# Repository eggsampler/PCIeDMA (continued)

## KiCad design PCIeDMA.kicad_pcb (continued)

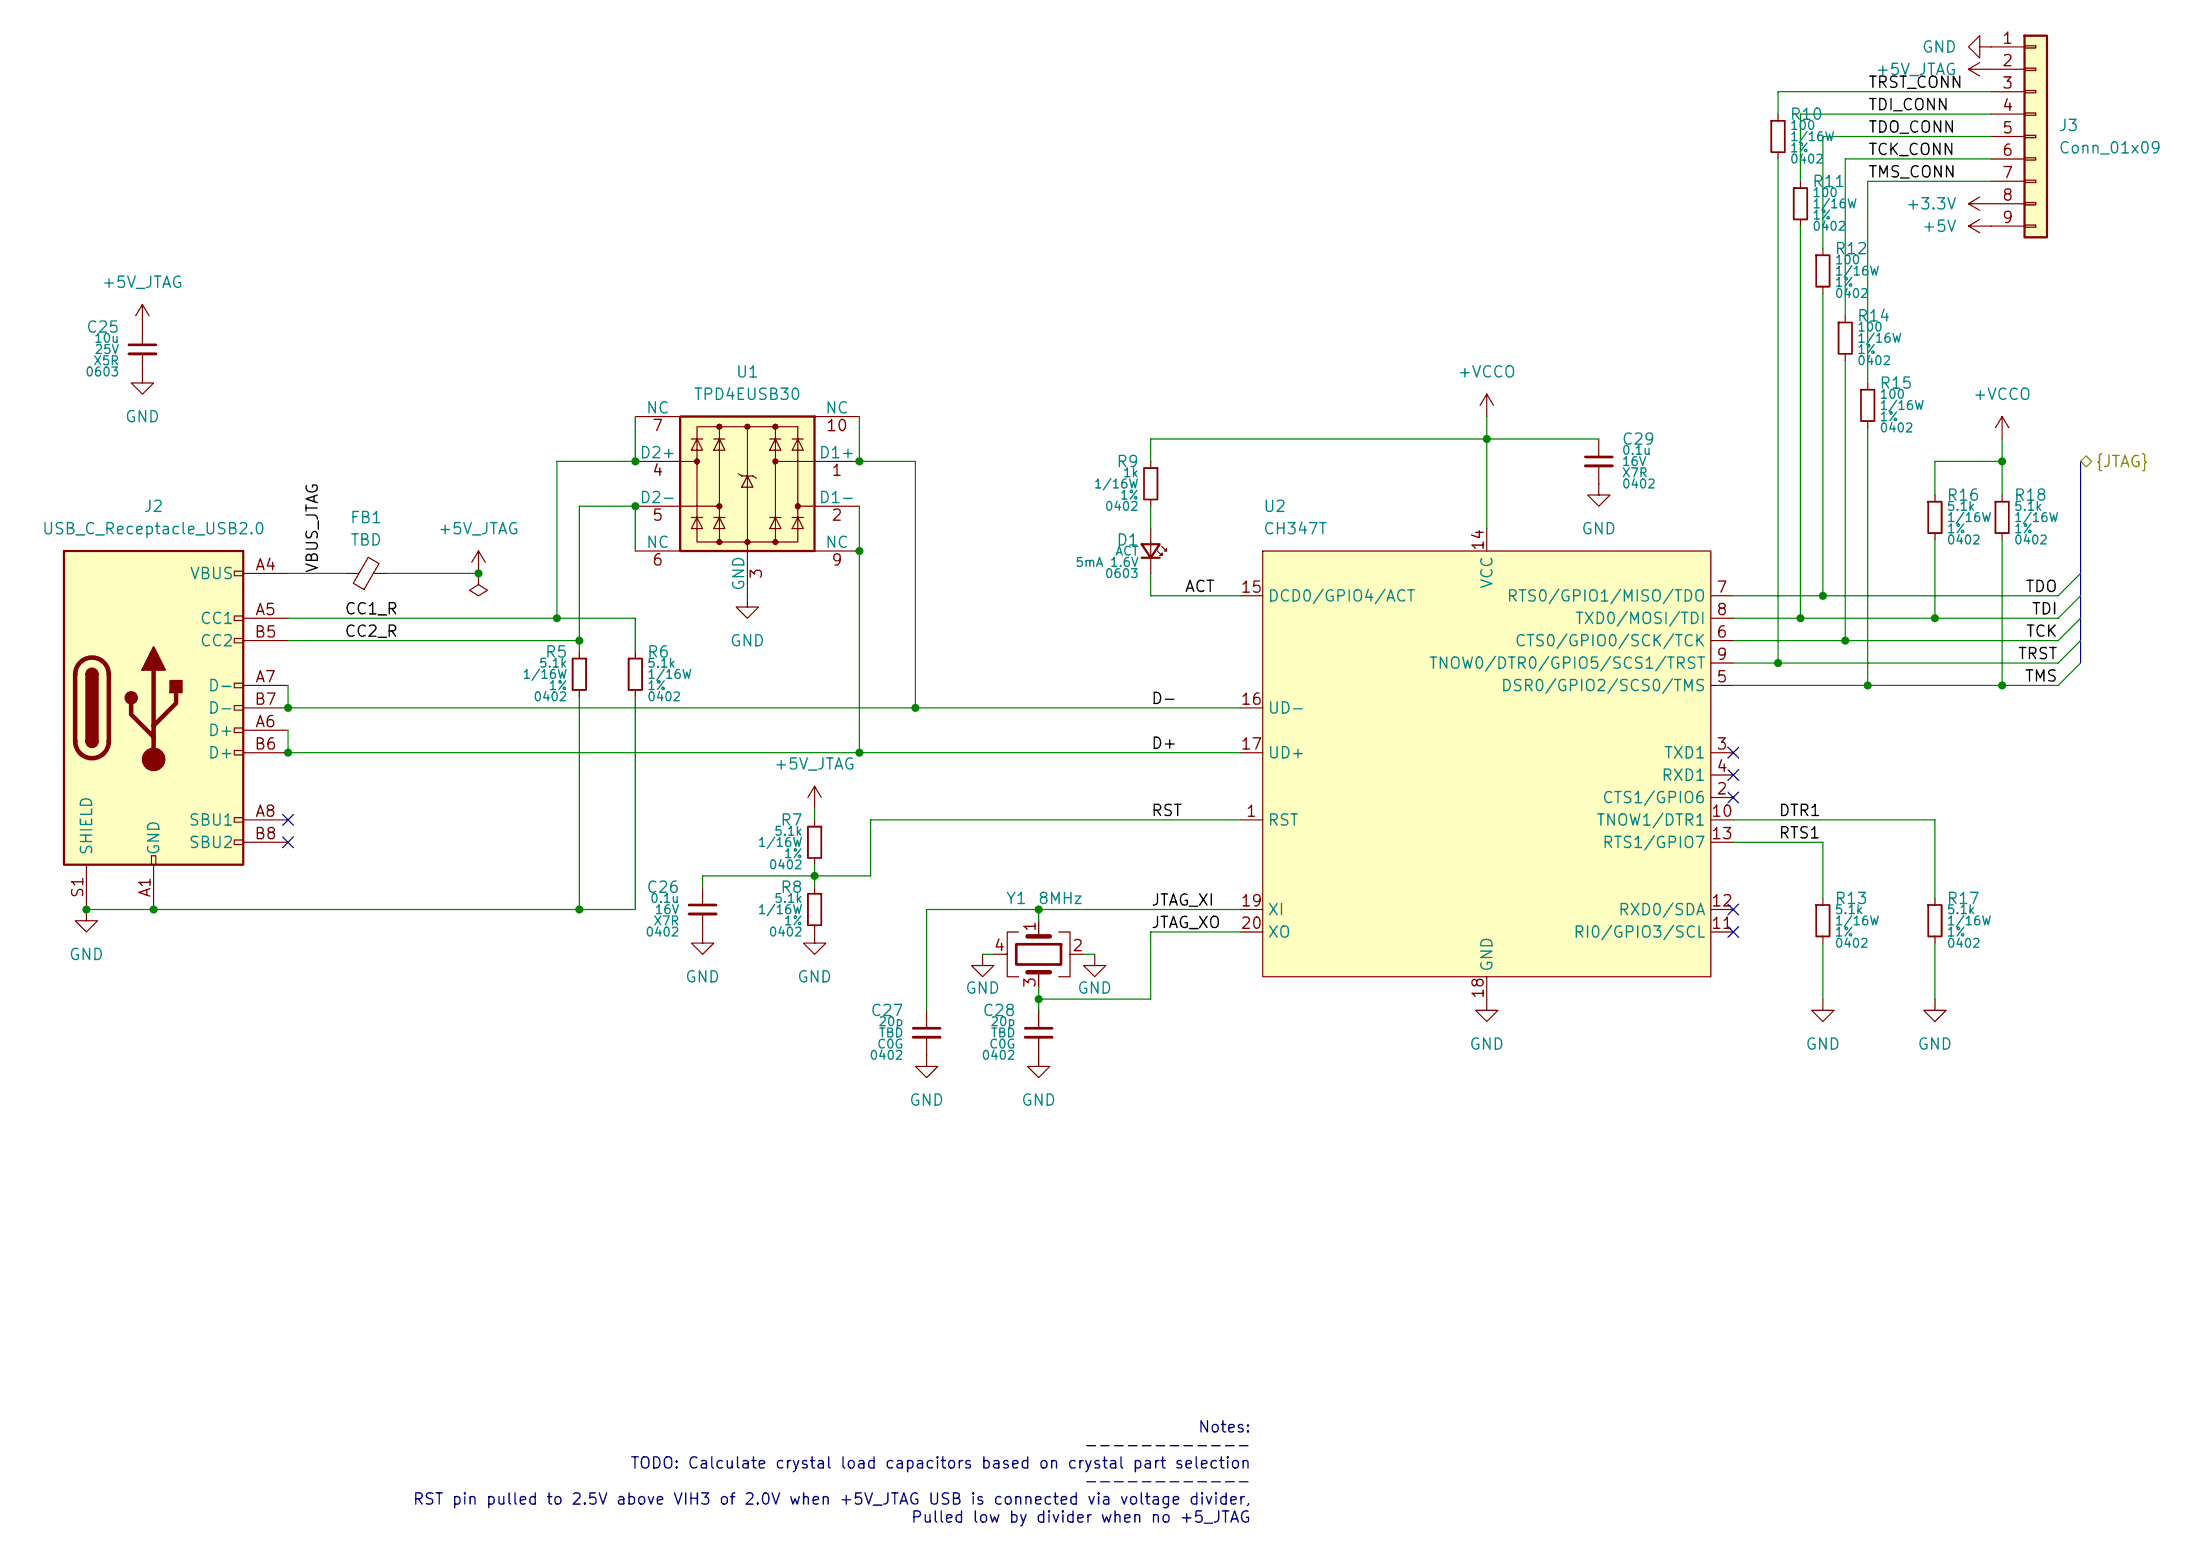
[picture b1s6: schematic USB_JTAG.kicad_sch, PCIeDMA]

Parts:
C25: 10u; C_0603_1608Metric; Rating 25V
C26, C29: 0.1u; C_0402_1005Metric; Rating 16V
C27, C28: 20p; C_0402_1005Metric; Rating TBD
D1: ACT; LED_0603_1608Metric; Rating 5mA 1.6V
FB1: TBD; L_0805_2012Metric
J2: USB_C_Receptacle_USB2.0; USB_C_Receptacle_HRO_TYPE-C-31-M-12
J3: Conn_01x09; PinHeader_1x09_P1.27mm_Vertical
R5, R6, R7, R8, R13, R16, R17, R18: 5.1k; R_0402_1005Metric; Rating 1/16W; Tolerance 1%
R9: 1k; R_0402_1005Metric; Rating 1/16W; Tolerance 1%
R10, R11, R12, R14, R15: 100; R_0402_1005Metric; Rating 1/16W; Tolerance 1%
U1: TPD4EUSB30; USON-10_2.5x1.0mm_P0.5mm
U2: CH347T; TSSOP-20_4.4x6.5mm_P0.65mm
Y1: 8MHz; Crystal_SMD_3225-4Pin_3.2x2.5mm

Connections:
+3.3V: J3.8; also elsewhere on the board
+5V: J3.9; also elsewhere on the board
+5V_JTAG: C25.1, FB1.2, J3.2, R7.1; also elsewhere on the board
+VCCO: C29.1, R9.1, R16.1, R18.1, U2.14 (VCC); also elsewhere on the board
/FPGA/TCK: R14.2, U2.6 (CTS0/GPIO0/SCK/TCK); also elsewhere on the board
/FPGA/TDI: R11.2, R16.2, U2.8 (TXD0/MOSI/TDI); also elsewhere on the board
/FPGA/TDO: R12.2, U2.7 (RTS0/GPIO1/MISO/TDO); also elsewhere on the board
/FPGA/TMS: R15.2, R18.2, U2.5 (DSR0/GPIO2/SCS0/TMS); also elsewhere on the board
/FPGA/TRST: R10.2, U2.9 (TNOW0/DTR0/GPIO5/SCS1/TRST); also elsewhere on the board
/USB JTAG/ACT: D1.1 (K), U2.15 (DCD0/GPIO4/ACT)
/USB JTAG/CC1_R: J2.A5 (CC1), R6.1, U1.4 (D2+), U1.7 (NC)
/USB JTAG/CC2_R: J2.B5 (CC2), R5.1, U1.5 (D2-), U1.6 (NC)
/USB JTAG/D+: J2.A6 (D+), J2.B6 (D+), U1.2 (D1-), U1.9 (NC), U2.17 (UD+)
/USB JTAG/D-: J2.A7 (D-), J2.B7 (D-), U1.1 (D1+), U1.10 (NC), U2.16 (UD-)
/USB JTAG/DTR1: R17.1, U2.10 (TNOW1/DTR1)
/USB JTAG/JTAG_XI: C27.1, U2.19 (XI), Y1.1
/USB JTAG/JTAG_XO: C28.1, U2.20 (XO), Y1.3
/USB JTAG/RST: C26.1, R7.2, R8.1, U2.1 (RST)
/USB JTAG/RTS1: R13.1, U2.13 (RTS1/GPIO7)
/USB JTAG/TCK_CONN: J3.6, R14.1
/USB JTAG/TDI_CONN: J3.4, R11.1
/USB JTAG/TDO_CONN: J3.5, R12.1
/USB JTAG/TMS_CONN: J3.7, R15.1
/USB JTAG/TRST_CONN: J3.3, R10.1
/USB JTAG/VBUS_JTAG: FB1.1, J2.A4 (VBUS), J2.A9 (VBUS), J2.B4 (VBUS), J2.B9 (VBUS)
GND: C25.2, C26.2, C27.2, C28.2, C29.2, J2.A1 (GND), J2.A12 (GND), J2.B1 (GND), J2.B12 (GND), J2.S1 (SHIELD), J3.1, R5.2, R6.2, R8.2, R13.2, R17.2, U1.3 (GND), U1.8 (GND), U2.18 (GND), Y1.2, Y1.4; also elsewhere on the board
unnamed: D1.2 (A), R9.2

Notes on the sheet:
Notes: ------------ TODO: Calculate crystal load capacitors based on crystal part selection ------------ RST pin pulled to 2.5V above VIH3 of 2.0V when +5V_JTAG USB is connected via voltage divider, Pulled low by divider when no +5_JTAG

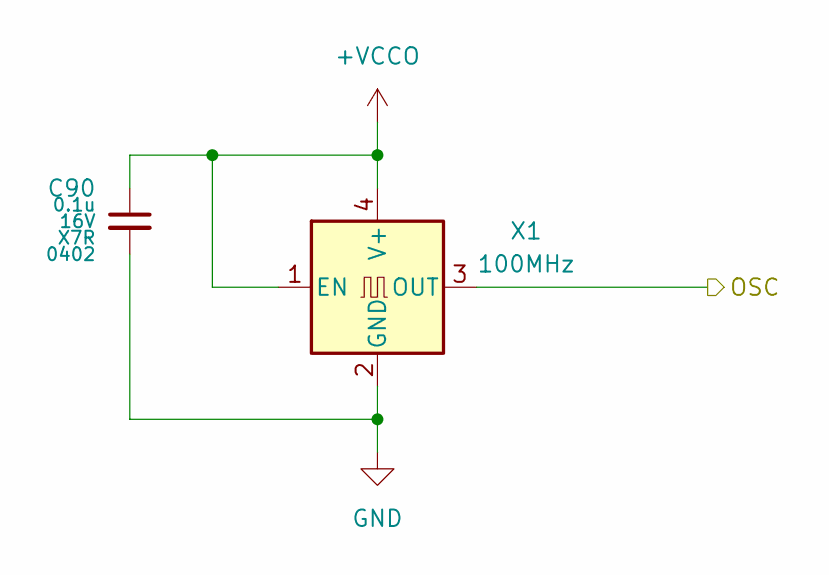
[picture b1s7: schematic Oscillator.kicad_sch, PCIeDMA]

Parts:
C90: 0.1u; C_0402_1005Metric; Rating 16V
X1: 100MHz; Crystal_SMD_3225-4Pin_3.2x2.5mm

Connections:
+VCCO: C90.1, X1.1 (EN), X1.4 (V+); also elsewhere on the board
/FPGA/OSC: X1.3 (OUT); also elsewhere on the board
GND: C90.2, X1.2 (GND); also elsewhere on the board

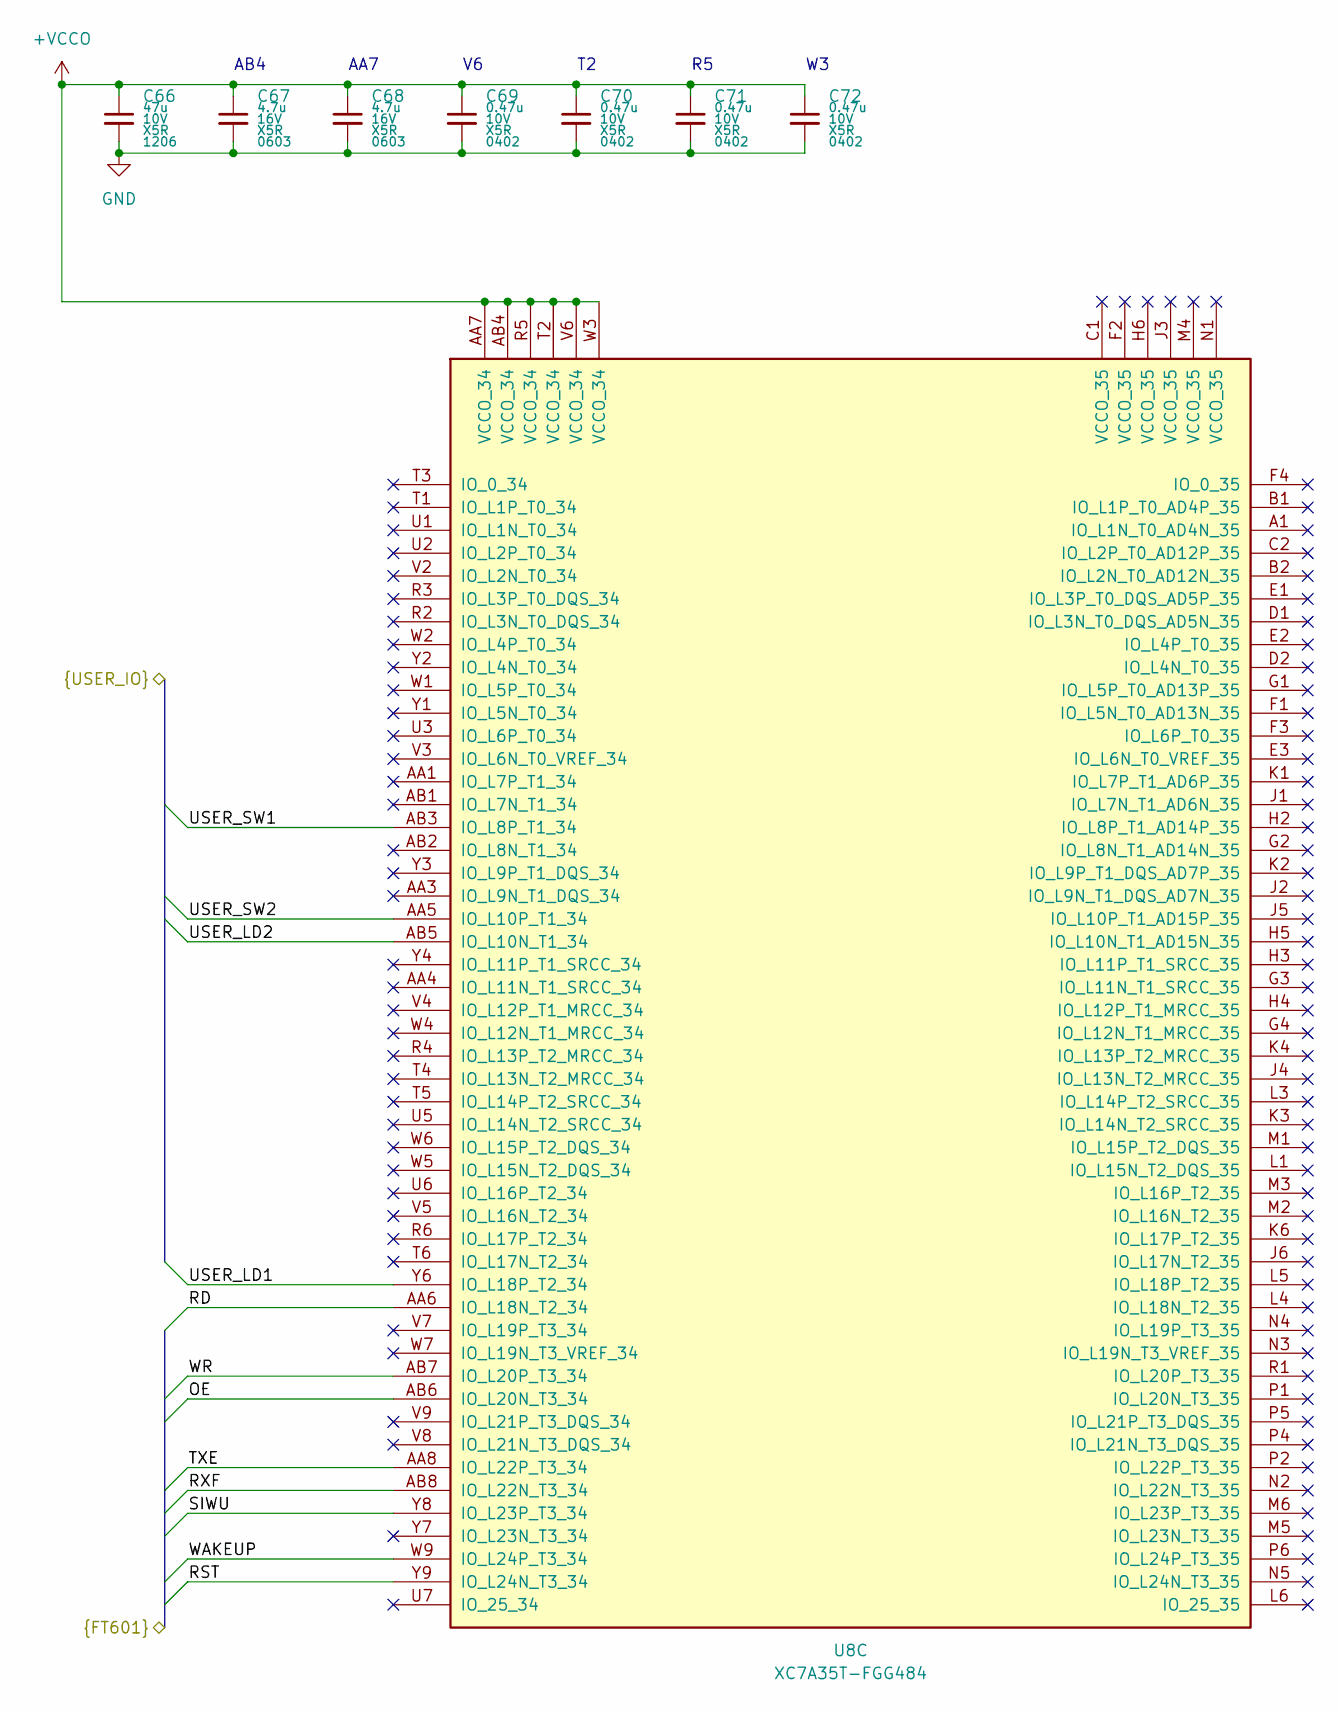
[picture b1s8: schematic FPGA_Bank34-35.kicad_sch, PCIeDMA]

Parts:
C66: 47u; C_1206_3216Metric; Rating 10V
C67, C68: 4.7u; C_0603_1608Metric; Rating 16V
C69, C70, C71, C72: 0.47u; C_0402_1005Metric; Rating 10V
U8: XC7A35T-FGG484; Xilinx_FGG484

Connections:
+VCCO: C66.1, C67.1, C68.1, C69.1, C70.1, C71.1, C72.1, U8.AA7 (VCCO_34), U8.AB4 (VCCO_34), U8.R5 (VCCO_34), U8.T2 (VCCO_34), U8.V6 (VCCO_34), U8.W3 (VCCO_34); also elsewhere on the board
/FPGA/OE: U8.AB6 (IO_L20N_T3_34); also elsewhere on the board
/FPGA/RD: U8.AA6 (IO_L18N_T2_34); also elsewhere on the board
/FPGA/RST: U8.Y9 (IO_L24N_T3_34); also elsewhere on the board
/FPGA/RXF: U8.AB8 (IO_L22N_T3_34); also elsewhere on the board
/FPGA/SIWU: U8.Y8 (IO_L23P_T3_34); also elsewhere on the board
/FPGA/TXE: U8.AA8 (IO_L22P_T3_34); also elsewhere on the board
/FPGA/USER_LD1: U8.Y6 (IO_L18P_T2_34); also elsewhere on the board
/FPGA/USER_LD2: U8.AB5 (IO_L10N_T1_34); also elsewhere on the board
/FPGA/USER_SW1: U8.AB3 (IO_L8P_T1_34); also elsewhere on the board
/FPGA/USER_SW2: U8.AA5 (IO_L10P_T1_34); also elsewhere on the board
/FPGA/WAKEUP: U8.W9 (IO_L24P_T3_34); also elsewhere on the board
/FPGA/WR: U8.AB7 (IO_L20P_T3_34); also elsewhere on the board
GND: C66.2, C67.2, C68.2, C69.2, C70.2, C71.2, C72.2; also elsewhere on the board

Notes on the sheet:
AB4
AA7

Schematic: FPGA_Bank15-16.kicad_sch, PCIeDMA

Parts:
C51: 47u; C_1206_3216Metric; Rating 10V
C52, C53: 4.7u; C_0603_1608Metric; Rating 16V
C54, C55, C56, C57: 0.47u; C_0402_1005Metric; Rating 10V
U8: XC7A35T-FGG484; Xilinx_FGG484

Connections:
+VCCO: C51.1, C52.1, C53.1, C54.1, C55.1, C56.1, C57.1, U8.A17 (VCCO_16), U8.B14 (VCCO_16), U8.C21 (VCCO_16), U8.D18 (VCCO_16), U8.E15 (VCCO_16), U8.F22 (VCCO_16); also elsewhere on the board
/FPGA/OSC: U8.B17 (IO_L11P_T1_SRCC_16); also elsewhere on the board
/FPGA/PCIE.SCL: U8.A16 (IO_L9N_T1_DQS_16); also elsewhere on the board
/FPGA/PCIE.SDA: U8.A15 (IO_L9P_T1_DQS_16); also elsewhere on the board
/FPGA/PERST: U8.B13 (IO_L8N_T1_16); also elsewhere on the board
/FPGA/TRST: U8.F21 (IO_25_16); also elsewhere on the board
/FPGA/WAKE: U8.A14 (IO_L10N_T1_16); also elsewhere on the board
GND: C51.2, C52.2, C53.2, C54.2, C55.2, C56.2, C57.2; also elsewhere on the board

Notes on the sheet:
A17
D18
B14
E15
C21
F22
Notes: ------------ UG483: Table 2-2: Required PCB Capacitor Quantities per Device: Artix-7 Devices Page 16, row FGG484 XC7A35T VCCO (all other Banks, per Bank): 1x47uF, 2x4.7uF, 4x0.47uF ------------ UG483: Page 36 Power Supply Consolidation Powering 1.8V VCCO, VCCAUX, and VCCAUX_IO from a common 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

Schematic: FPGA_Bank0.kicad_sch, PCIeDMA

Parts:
C58: 47u; C_1206_3216Metric; Rating 10V
D4: DONE; LED_0603_1608Metric; Rating 5mA 1.6V
D5: INIT_B; LED_0603_1608Metric; Rating 5mA 1.6V
R31, R32, R33, R34, R35, R36, R37, R38: 1k; R_0402_1005Metric; Rating 1/16W; Tolerance 1%
SW3: PROGRAM; SW_SPST_B3U-1000P
SW4: INIT_B; SW_SPST_B3U-1000P
U8: XC7A35T-FGG484; Xilinx_FGG484

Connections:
+VCCO: C58.1, R31.1, R32.1, R33.1, R34.1, R37.1, R38.1, U8.F12 (VCCO_0), U8.T12 (VCCO_0), U8.U8 (CFGBVS_0); also elsewhere on the board
/FPGA/Bank 0/DONE: D4.1 (K), R32.2, U8.G11 (DONE_0)
/FPGA/Bank 0/INIT_B: D5.1 (K), R37.2, SW4.2, U8.U12 (INIT_B_0)
/FPGA/Bank 0/M0: R33.2, U8.U11 (M0_0)
/FPGA/Bank 0/M1: R35.1, U8.U10 (M1_0)
/FPGA/Bank 0/M2: R36.1, U8.U9 (M2_0)
/FPGA/Bank 0/PROGRAM_B: R31.2, SW3.2, U8.N12 (PROGRAM_B_0)
/FPGA/QCLK: U8.L12 (CCLK_0); also elsewhere on the board
/FPGA/TCK: U8.V12 (TCK_0); also elsewhere on the board
/FPGA/TDI: U8.R13 (TDI_0); also elsewhere on the board
/FPGA/TDO: U8.U13 (TDO_0); also elsewhere on the board
/FPGA/TMS: U8.T13 (TMS_0); also elsewhere on the board
GND: C58.2, R35.2, R36.2, SW3.1, SW4.1, U8.L9 (VREFN_0), U8.L10 (VP_0), U8.M9 (VN_0), U8.M10 (VREFP_0), U8.N9 (DXN_0), U8.N10 (DXP_0); also elsewhere on the board
unnamed: D4.2 (A), R34.2
unnamed: D5.2 (A), R38.2

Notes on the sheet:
Notes: ------------ UG470 Page 21 Table 2-4: Configuration Pin Definitions (Cont'd) Connect PROGRAM_B to an external ≤ 4.7 kΩ pull-up resistor to VCCO_0 to ensure a stable High input, and recommend push-button to GND to enable manual configuration reset. ------------ UG470 Page 21 Table 2-4: Config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
Notes: ------------ UG483: Table 2-2: Required PCB Capacitor Quantities per Device: Artix-7 Devices Page 16, row FGG484 XC7A35T VCCO (bank 0): 1x47uF ------------ UG470: Page 28 Configuration Banks Voltage Select CFGVBS pulled low for 1.8V or 1.5V JTAG operation ------------ UG470 Page 7 The specif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

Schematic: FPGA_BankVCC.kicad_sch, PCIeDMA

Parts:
C73: 100u; C_1206_3216Metric; Rating 6.3V
C74, C75: 47u; C_1206_3216Metric; Rating 10V
C76, C77, C79, C80: 4.7u; C_0603_1608Metric; Rating 16V
C78, C81, C82, C83, C84, C85, C86, C87, C88: 0.47u; C_0402_1005Metric; Rating 10V
U8: XC7A35T-FGG484; Xilinx_FGG484

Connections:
+VCCAUX: C74.1, C77.1, C80.1, C82.1, C84.1, C86.1, C87.1, C88.1, U8.H12 (VCCAUX), U8.K10 (VCCADC_0), U8.K12 (VCCAUX), U8.M12 (VCCAUX), U8.P12 (VCCAUX), U8.R11 (VCCAUX); also elsewhere on the board
+VCCINT: C73.1, C75.1, C76.1, C78.1, C79.1, C81.1, C83.1, C85.1, U8.H8 (VCCINT), U8.H10 (VCCINT), U8.J7 (VCCINT), U8.J9 (VCCINT), U8.J11 (VCCBRAM), U8.K8 (VCCINT), U8.L7 (VCCINT), U8.L11 (VCCBRAM), U8.M8 (VCCINT), U8.N7 (VCCINT), U8.N11 (VCCBRAM), U8.P8 (VCCINT), U8.P10 (VCCINT), U8.R7 (VCCINT), U8.R9 (VCCINT), U8.T8 (VCCINT), U8.T10 (VCCINT); also elsewhere on the board
GND: C73.2, C74.2, C75.2, C76.2, C77.2, C78.2, C79.2, C80.2, C81.2, C82.2, C83.2, C84.2, C85.2, C86.2, C87.2, C88.2, U8.A2 (GND), U8.A3 (GND), U8.A5 (GND), U8.A7 (GND), U8.A9 (GND), U8.A11 (GND), U8.A12 (GND), U8.A22 (GND), U8.AA2 (GND), U8.AA12 (GND), U8.AA22 (GND), U8.AB9 (GND), U8.AB19 (GND), U8.B3 (GND), U8.B12 (GND), U8.B19 (GND), U8.C3 (GND), U8.C6 (GND), U8.C10 (GND), U8.C12 (GND), U8.C16 (GND), U8.D3 (GND), U8.D4 (GND), U8.D8 (GND), U8.D12 (GND), U8.D13 (GND), U8.E4 (GND), U8.E5 (GND), U8.E7 (GND), U8.E9 (GND), U8.E11 (GND), U8.E12 (VCCBATT_0), U8.E20 (GND), U8.F5 (GND), U8.F11 (GND), U8.F17 (GND), U8.G5 (GND), U8.G6 (GND), U8.G7 (GND), U8.G8 (GND), U8.G9 (GND), U8.G10 (GND), U8.G12 (GND), U8.G14 (GND), U8.H1 (GND), U8.H7 (GND), U8.H9 (GND), U8.H11 (GND), U8.H21 (GND), U8.J8 (GND), U8.J10 (GND), U8.J12 (GND), U8.J18 (GND), U8.K5 (GND), U8.K7 (GND), U8.K9 (GNDADC_0), U8.K11 (GND), U8.K15 (GND), U8.L2 (GND), U8.L8 (GND), U8.L22 (GND), U8.M7 (GND), U8.M11 (GND), U8.M19 (GND), U8.N6 (GND), U8.N8 (GND), U8.N16 (GND), U8.P3 (GND), U8.P7 (GND), U8.P9 (GND), U8.P11 (GND), U8.P13 (GND), U8.R8 (GND), U8.R10 (GND), U8.R12 (GND), U8.R20 (GND), U8.T7 (GND), U8.T9 (GND), U8.T11 (GND), U8.T17 (GND), U8.U4 (GND), U8.U14 (GND), U8.V1 (GND), U8.V11 (GND), U8.V21 (GND), U8.W8 (GND), U8.W18 (GND), U8.Y5 (GND), U8.Y15 (GND); also elsewhere on the board

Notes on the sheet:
K12
(For VCCBRAM)
Notes: ------------ UG483: Table 2-2: Required PCB Capacitor Quantities per Device: Artix-7 Devices Page 16, row FGG484 XC7A35T VCCINT: 1x100uF, 2x4.7uF, 3x0.47uF VCCBRAM: 1x47uF, 1x0.47uF VCCAUX: 1x47uF, 2x4.7uF, 5x0.47uF ------------ UG483: Page 19: Table 2-5: PCB Capacitor Specifications 100uF: 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
R11
H12
P12
J11
M12
K10

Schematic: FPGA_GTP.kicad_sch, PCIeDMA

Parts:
C45, C46, C49, C50: 0.1u; C_0402_1005Metric; Rating 16V
C47, C48: 4.7u; C_0603_1608Metric; Rating 16V
R30: 100; R_0402_1005Metric; Rating 1/16W; Tolerance 1%
U8: XC7A35T-FGG484; Xilinx_FGG484

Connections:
+MGTAVCC: C45.1, C46.1, C47.1, U8.D6 (MGTAVCC), U8.D10 (MGTAVCC), U8.E8 (MGTAVCC), U8.F7 (MGTAVCC), U8.F9 (MGTAVCC); also elsewhere on the board
+MGTAVTT: C48.1, C49.1, C50.1, R30.1, U8.B5 (MGTAVTT), U8.B7 (MGTAVTT), U8.B9 (MGTAVTT), U8.B11 (MGTAVTT), U8.C4 (MGTAVTT), U8.C8 (MGTAVTT); also elsewhere on the board
/FPGA/CLK_N: U8.E10 (MGTREFCLK1N_216); also elsewhere on the board
/FPGA/CLK_P: U8.F10 (MGTREFCLK1P_216); also elsewhere on the board
/FPGA/GTP/MGTRREF: R30.2, U8.F8 (MGTRREF_216)
/FPGA/RX0_N: U8.A8 (MGTPRXN0_216); also elsewhere on the board
/FPGA/RX0_P: U8.B8 (MGTPRXP0_216); also elsewhere on the board
/FPGA/RX1_N: U8.C11 (MGTPRXN1_216); also elsewhere on the board
/FPGA/RX1_P: U8.D11 (MGTPRXP1_216); also elsewhere on the board
/FPGA/RX2_N: U8.A10 (MGTPRXN2_216); also elsewhere on the board
/FPGA/RX2_P: U8.B10 (MGTPRXP2_216); also elsewhere on the board
/FPGA/RX3_N: U8.C9 (MGTPRXN3_216); also elsewhere on the board
/FPGA/RX3_P: U8.D9 (MGTPRXP3_216); also elsewhere on the board
/FPGA/TX0_N: U8.A4 (MGTPTXN0_216); also elsewhere on the board
/FPGA/TX0_P: U8.B4 (MGTPTXP0_216); also elsewhere on the board
/FPGA/TX1_N: U8.C5 (MGTPTXN1_216); also elsewhere on the board
/FPGA/TX1_P: U8.D5 (MGTPTXP1_216); also elsewhere on the board
/FPGA/TX2_N: U8.A6 (MGTPTXN2_216); also elsewhere on the board
/FPGA/TX2_P: U8.B6 (MGTPTXP2_216); also elsewhere on the board
/FPGA/TX3_N: U8.C7 (MGTPTXN3_216); also elsewhere on the board
/FPGA/TX3_P: U8.D7 (MGTPTXP3_216); also elsewhere on the board
GND: C45.2, C46.2, C47.2, C48.2, C49.2, C50.2; also elsewhere on the board

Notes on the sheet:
Notes: ------------ DS181 Page 2, Table 2: Recommended Operating Conditions VMGTAVCC: Typical 1.0V VMGTAVTT: Typical 1.2V ------------ UG482 Table 5-14: MGTRREF - Connect to a 100Ω resistor that is also connected to MGTAVTT Termination Resistor Calibration Circuit: The MGTRREF pin should be connect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
B11
D10

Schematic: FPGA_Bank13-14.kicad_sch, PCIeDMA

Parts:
C59: 47u; C_1206_3216Metric; Rating 10V
C60, C61: 4.7u; C_0603_1608Metric; Rating 16V
C62, C63, C64, C65: 0.47u; C_0402_1005Metric; Rating 10V
R39: 1k; R_0402_1005Metric; Rating 1/16W; Tolerance 1%
U8: XC7A35T-FGG484; Xilinx_FGG484

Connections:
+VCCO: C59.1, C60.1, C61.1, C62.1, C63.1, C64.1, C65.1, R39.1, U8.M14 (VCCO_14), U8.P18 (VCCO_14), U8.R15 (VCCO_14), U8.T22 (VCCO_14), U8.U19 (VCCO_14), U8.Y20 (VCCO_14); also elsewhere on the board
/FPGA/BE0: U8.Y18 (IO_L13P_T2_MRCC_14); also elsewhere on the board
/FPGA/BE1: U8.AA18 (IO_L17P_T2_A14_D30_14); also elsewhere on the board
/FPGA/BE2: U8.AB18 (IO_L17N_T2_A13_D29_14); also elsewhere on the board
/FPGA/BE3: U8.W17 (IO_L16N_T2_A15_D31_14); also elsewhere on the board
/FPGA/Bank 13-14/PUDC_B: R39.2, U8.U22 (IO_L3P_T0_DQS_PUDC_B_14)
/FPGA/CLK: U8.W19 (IO_L12P_T1_MRCC_14); also elsewhere on the board
/FPGA/CS: U8.T19 (IO_L6P_T0_FCS_B_14); also elsewhere on the board
/FPGA/D0: U8.P22 (IO_L1P_T0_D00_MOSI_14); also elsewhere on the board
/FPGA/D1: U8.R22 (IO_L1N_T0_D01_DIN_14); also elsewhere on the board
/FPGA/D2: U8.P21 (IO_L2P_T0_D02_14); also elsewhere on the board
/FPGA/D3: U8.R21 (IO_L2N_T0_D03_14); also elsewhere on the board
/FPGA/DATA0: U8.N13 (IO_L23P_T3_A03_D19_14); also elsewhere on the board
/FPGA/DATA1: U8.N14 (IO_L23N_T3_A02_D18_14); also elsewhere on the board
/FPGA/DATA2: U8.N15 (IO_25_14); also elsewhere on the board
/FPGA/DATA3: U8.P15 (IO_L22P_T3_A05_D21_14); also elsewhere on the board
/FPGA/DATA4: U8.P16 (IO_L24P_T3_A01_D17_14); also elsewhere on the board
/FPGA/DATA5: U8.N17 (IO_L21P_T3_DQS_14); also elsewhere on the board
/FPGA/DATA6: U8.P17 (IO_L21N_T3_DQS_A06_D22_14); also elsewhere on the board
/FPGA/DATA7: U8.R17 (IO_L24N_T3_A00_D16_14); also elsewhere on the board
/FPGA/DATA8: U8.P19 (IO_L5P_T0_D06_14); also elsewhere on the board
/FPGA/DATA9: U8.R18 (IO_L20P_T3_A08_D24_14); also elsewhere on the board
/FPGA/DATA10: U8.R19 (IO_L5N_T0_D07_14); also elsewhere on the board
/FPGA/DATA11: U8.T18 (IO_L20N_T3_A07_D23_14); also elsewhere on the board
/FPGA/DATA12: U8.U18 (IO_L18N_T2_A11_D27_14); also elsewhere on the board
/FPGA/DATA13: U8.V18 (IO_L14P_T2_SRCC_14); also elsewhere on the board
/FPGA/DATA14: U8.V19 (IO_L14N_T2_SRCC_14); also elsewhere on the board
/FPGA/DATA15: U8.V17 (IO_L16P_T2_CSI_B_14); also elsewhere on the board
/FPGA/DATA16: U8.W20 (IO_L12N_T1_MRCC_14); also elsewhere on the board
/FPGA/DATA17: U8.Y19 (IO_L13N_T2_MRCC_14); also elsewhere on the board
/FPGA/DATA18: U8.T21 (IO_L4P_T0_D04_14); also elsewhere on the board
/FPGA/DATA19: U8.T20 (IO_L6N_T0_D08_VREF_14); also elsewhere on the board
/FPGA/DATA20: U8.U21 (IO_L4N_T0_D05_14); also elsewhere on the board
/FPGA/DATA21: U8.V20 (IO_L11N_T1_SRCC_14); also elsewhere on the board
/FPGA/DATA22: U8.W22 (IO_L7N_T1_D10_14); also elsewhere on the board
/FPGA/DATA23: U8.W21 (IO_L7P_T1_D09_14); also elsewhere on the board
/FPGA/DATA24: U8.Y22 (IO_L9N_T1_DQS_D13_14); also elsewhere on the board
/FPGA/DATA25: U8.Y21 (IO_L9P_T1_DQS_14); also elsewhere on the board
/FPGA/DATA26: U8.AA21 (IO_L8N_T1_D12_14); also elsewhere on the board
/FPGA/DATA27: U8.AB22 (IO_L10N_T1_D15_14); also elsewhere on the board
/FPGA/DATA28: U8.AA20 (IO_L8P_T1_D11_14); also elsewhere on the board
/FPGA/DATA29: U8.AB21 (IO_L10P_T1_D14_14); also elsewhere on the board
/FPGA/DATA30: U8.AA19 (IO_L15P_T2_DQS_RDWR_B_14); also elsewhere on the board
/FPGA/DATA31: U8.AB20 (IO_L15N_T2_DQS_DOUT_CSO_B_14); also elsewhere on the board
GND: C59.2, C60.2, C61.2, C62.2, C63.2, C64.2, C65.2; also elsewhere on the board

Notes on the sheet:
Notes: ------------ TODO: Determine if EMCCLK is needed or the internal clock is fine for QSPI Arty A7 toes EMCCLK to CCLK_0 via 49.9 resistor ------------ UG470 Page 22 Table 2-4: Configuration Pin Definitions (Cont'd) Active-Low PUDC_B input enables internal pull-up resistors on the SelectIO pins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
R15
P18
T22
M14
Y20
U19

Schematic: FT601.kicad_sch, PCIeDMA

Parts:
C40, C41, C42, C43: 0.1u; C_0402_1005Metric; Rating 16V
C44: 4.7u; C_0603_1608Metric; Rating 16V
R24: 10k; R_0402_1005Metric; Rating 1/16W; Tolerance 1%
R25: 1.6k; R_0402_1005Metric; Rating 1/16W; Tolerance 1%
U7: FT601Q; QFN-76-1EP_9x9mm_P0.4mm_EP5.81x6.31mm
Y2: 30MHz; Crystal_SMD_3225-4Pin_3.2x2.5mm

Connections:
+5V_DATA: U7.37 (VBUS); also elsewhere on the board
+VCCO: C42.1, R24.1, U7.14 (VCCIO), U7.20 (VCC33), U7.24 (VCC33), U7.28 (VDDA), U7.38 (VCC33), U7.49 (VCCIO), U7.59 (VCCIO), U7.68 (VCCIO); also elsewhere on the board
/FPGA/BE0: U7.4 (BE_0); also elsewhere on the board
/FPGA/BE1: U7.5 (BE_1); also elsewhere on the board
/FPGA/BE2: U7.6 (BE_2); also elsewhere on the board
/FPGA/BE3: U7.7 (BE_3); also elsewhere on the board
/FPGA/CLK: U7.58 (CLK); also elsewhere on the board
/FPGA/DATA0: U7.40 (DATA_0); also elsewhere on the board
/FPGA/DATA1: U7.41 (DATA_1); also elsewhere on the board
/FPGA/DATA2: U7.42 (DATA_2); also elsewhere on the board
/FPGA/DATA3: U7.43 (DATA_3); also elsewhere on the board
/FPGA/DATA4: U7.44 (DATA_4); also elsewhere on the board
/FPGA/DATA5: U7.45 (DATA_5); also elsewhere on the board
/FPGA/DATA6: U7.46 (DATA_6); also elsewhere on the board
/FPGA/DATA7: U7.47 (DATA_7); also elsewhere on the board
/FPGA/DATA8: U7.50 (DATA_8); also elsewhere on the board
/FPGA/DATA9: U7.51 (DATA_9); also elsewhere on the board
/FPGA/DATA10: U7.52 (DATA_10); also elsewhere on the board
/FPGA/DATA11: U7.53 (DATA_11); also elsewhere on the board
/FPGA/DATA12: U7.54 (DATA_12); also elsewhere on the board
/FPGA/DATA13: U7.55 (DATA_13); also elsewhere on the board
/FPGA/DATA14: U7.56 (DATA_14); also elsewhere on the board
/FPGA/DATA15: U7.57 (DATA_15); also elsewhere on the board
/FPGA/DATA16: U7.60 (DATA_16); also elsewhere on the board
/FPGA/DATA17: U7.61 (DATA_17); also elsewhere on the board
/FPGA/DATA18: U7.62 (DATA_18); also elsewhere on the board
/FPGA/DATA19: U7.63 (DATA_19); also elsewhere on the board
/FPGA/DATA20: U7.64 (DATA_20); also elsewhere on the board
/FPGA/DATA21: U7.65 (DATA_21); also elsewhere on the board
/FPGA/DATA22: U7.66 (DATA_22); also elsewhere on the board
/FPGA/DATA23: U7.67 (DATA_23); also elsewhere on the board
/FPGA/DATA24: U7.69 (DATA_24); also elsewhere on the board
/FPGA/DATA25: U7.70 (DATA_25); also elsewhere on the board
/FPGA/DATA26: U7.71 (DATA_26); also elsewhere on the board
/FPGA/DATA27: U7.72 (DATA_27); also elsewhere on the board
/FPGA/DATA28: U7.73 (DATA_28); also elsewhere on the board
/FPGA/DATA29: U7.74 (DATA_29); also elsewhere on the board
/FPGA/DATA30: U7.75 (DATA_30); also elsewhere on the board
/FPGA/DATA31: U7.76 (DATA_31); also elsewhere on the board
/FPGA/OE: U7.13 (OE_N); also elsewhere on the board
/FPGA/RD: U7.12 (RD_N); also elsewhere on the board
/FPGA/RST: C43.1, R24.2, U7.15 (RESET_N); also elsewhere on the board
/FPGA/RXF: U7.9 (RXF_N); also elsewhere on the board
/FPGA/SIWU: U7.10 (SIWU_N); also elsewhere on the board
/FPGA/TXE: U7.8 (TXE_N); also elsewhere on the board
/FPGA/WAKEUP: U7.16 (WAKEUP_N); also elsewhere on the board
/FPGA/WR: U7.11 (WR_N); also elsewhere on the board
/USB Data/FT601/DM: U7.25 (DM); also elsewhere on the board
/USB Data/FT601/DP: U7.23 (DP); also elsewhere on the board
/USB Data/FT601/FT601_XI: C40.1, U7.17 (XI), Y2.1
/USB Data/FT601/FT601_XO: C41.1, U7.18 (XO), Y2.3
/USB Data/FT601/RIDN: U7.34 (RIDN); also elsewhere on the board
/USB Data/FT601/RIDP: U7.35 (RIDP); also elsewhere on the board
/USB Data/FT601/RREF: R25.1, U7.27 (RREF)
/USB Data/FT601/TODN: U7.31 (TODN); also elsewhere on the board
/USB Data/FT601/TODP: U7.32 (TODP); also elsewhere on the board
/USB Data/FT601/VD10: C44.1, U7.2 (AVDD), U7.3 (VD10), U7.30 (VD10), U7.33 (VD10), U7.39 (DV10), U7.48 (VD10)
GND: C40.2, C41.2, C42.2, C43.2, C44.2, R25.2, U7.1 (GND), U7.26 (GND), U7.29 (GND), U7.36 (GND), U7.77 (EP), Y2.2, Y2.4; also elsewhere on the board

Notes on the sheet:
AC coupling caps on mux sheet

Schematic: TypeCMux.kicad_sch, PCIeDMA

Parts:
C31, C32, C33, C34, C35, C36, C37, C39: 0.1u; C_0402_1005Metric; Rating 16V
C38: 0.47u; C_0402_1005Metric; Rating 10V
Q1: Q_NMOS_DGS; SOT-23
R19: 900k; R_1206_3216Metric; Rating 0.1W; Tolerance 1%
R20: 200k; R_0402_1005Metric; Rating 1/16W; Tolerance 1%
R21, R22, R23: 10k; R_0402_1005Metric; Rating 1/16W; Tolerance 1%
U6: HD3SS3220

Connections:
+5V_DATA: C35.1, R19.1, R22.2, R23.1, U6.30 (VDD5); also elsewhere on the board
+VCCO: C36.1, R20.1, R21.1, U6.8 (VCC33); also elsewhere on the board
/USB Data/FT601/RIDN: U6.10 (RXn); also elsewhere on the board
/USB Data/FT601/RIDP: U6.9 (RXp); also elsewhere on the board
/USB Data/FT601/TODN: C37.2; also elsewhere on the board
/USB Data/FT601/TODP: C39.2; also elsewhere on the board
/USB Data/Type C Mux/CC1: U6.2 (CC1); also elsewhere on the board
/USB Data/Type C Mux/CC2: U6.1 (CC2); also elsewhere on the board
/USB Data/Type C Mux/DIR: R20.2, U6.11 (DIR)
/USB Data/Type C Mux/ENn: Q1.1 (D), R21.2, U6.12 (ENn_MUX), U6.29 (ENn_CC)
/USB Data/Type C Mux/ENn_G: C38.1, Q1.2 (G), R22.1
/USB Data/Type C Mux/RX1n: U6.14 (RX1n); also elsewhere on the board
/USB Data/Type C Mux/RX1p: U6.15 (RX1p); also elsewhere on the board
/USB Data/Type C Mux/RX2n: U6.18 (RX2n); also elsewhere on the board
/USB Data/Type C Mux/RX2p: U6.19 (RX2p); also elsewhere on the board
/USB Data/Type C Mux/TOD_C_n: C37.1, U6.7 (TXn)
/USB Data/Type C Mux/TOD_C_p: C39.1, U6.6 (TXp)
/USB Data/Type C Mux/TX1_C_n: C33.2, U6.16 (TX1n)
/USB Data/Type C Mux/TX1_C_p: C31.2, U6.17 (TX1p)
/USB Data/Type C Mux/TX1n: C31.1; also elsewhere on the board
/USB Data/Type C Mux/TX1p: C33.1; also elsewhere on the board
/USB Data/Type C Mux/TX2_C_n: C34.2, U6.20 (TX2n)
/USB Data/Type C Mux/TX2_C_p: C32.2, U6.21 (TX2p)
/USB Data/Type C Mux/TX2n: C32.1; also elsewhere on the board
/USB Data/Type C Mux/TX2p: C34.1; also elsewhere on the board
/USB Data/Type C Mux/VBUS_DET: R19.2, U6.5 (VBUS_DET)
GND: C35.2, C36.2, C38.2, Q1.3 (S), R23.2, U6.4 (PORT), U6.13 (GND), U6.28 (GND), U6.31 (EP); also elsewhere on the board

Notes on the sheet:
HD3SS3220 Does Not Care About Differential Pair Polarity
NC = GPIO mode
Ingored in UFP
Requires 200k pu
Don't care in UFP
Notes: ------------ 7.3.12 VDD5 and VCC33 Power-On Requirements The HD3SS3220 has two power supplies: VDD5 and VCC33. The VDD5 supply powers the internal CC controller and also provides VCONN to either CC1 or CC2. The VCC33 powers the 2:1 MUX. The HD3SS3220 non-failsafe pins are the following: PORT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
Notes: ------------ Schematic based on datasheet 8.2.4 UFP port
Port low = UFP mode UFP mode is pulldowns on both CC pins

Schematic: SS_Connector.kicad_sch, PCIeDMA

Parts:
C30: 10u; C_0603_1608Metric; Rating 25V
FB2: TBD; L_0805_2012Metric
J4: USB_C_Receptacle; USB_C_Receptacle_Molex_105450-0101
U3, U4, U5: TPD4EUSB30; USON-10_2.5x1.0mm_P0.5mm

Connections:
+5V_DATA: C30.1, FB2.2; also elsewhere on the board
/USB Data/FT601/DM: J4.A7 (D-), J4.B7 (D-), U3.5 (D2-), U3.6 (NC); also elsewhere on the board
/USB Data/FT601/DP: J4.A6 (D+), J4.B6 (D+), U3.4 (D2+), U3.7 (NC); also elsewhere on the board
/USB Data/Type C Mux/CC1: J4.A5 (CC1), U3.1 (D1+), U3.10 (NC); also elsewhere on the board
/USB Data/Type C Mux/CC2: J4.B5 (CC2), U3.2 (D1-), U3.9 (NC); also elsewhere on the board
/USB Data/Type C Mux/RX1n: J4.B10 (RX1-), U4.1 (D1+), U4.10 (NC); also elsewhere on the board
/USB Data/Type C Mux/RX1p: J4.B11 (RX1+), U4.2 (D1-), U4.9 (NC); also elsewhere on the board
/USB Data/Type C Mux/RX2n: J4.A10 (RX2-), U5.1 (D1+), U5.10 (NC); also elsewhere on the board
/USB Data/Type C Mux/RX2p: J4.A11 (RX2+), U5.2 (D1-), U5.9 (NC); also elsewhere on the board
/USB Data/Type C Mux/TX1n: J4.A3 (TX1-), U4.5 (D2-), U4.6 (NC); also elsewhere on the board
/USB Data/Type C Mux/TX1p: J4.A2 (TX1+), U4.4 (D2+), U4.7 (NC); also elsewhere on the board
/USB Data/Type C Mux/TX2n: J4.B3 (TX2-), U5.5 (D2-), U5.6 (NC); also elsewhere on the board
/USB Data/Type C Mux/TX2p: J4.B2 (TX2+), U5.4 (D2+), U5.7 (NC); also elsewhere on the board
/USB Data/Type C SS Connector/VBUS_DATA: FB2.1, J4.A4 (VBUS), J4.A9 (VBUS), J4.B4 (VBUS), J4.B9 (VBUS)
GND: C30.2, J4.A1 (GND), J4.A12 (GND), J4.B1 (GND), J4.B12 (GND), J4.S1 (SHIELD), U3.3 (GND), U3.8 (GND), U4.3 (GND), U4.8 (GND), U5.3 (GND), U5.8 (GND); also elsewhere on the board

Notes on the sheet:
Notes: ------------ +5V_Data is used for the mux and FT601 ------------ TPD4EUSB30 is used instead of a single part to simplify the BOM, as this can be used for the jtag interface too.

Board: 8 copper layers, 235 parts (99 on the bottom side), 207 nets, no tracks yet.

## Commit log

2023-02-20 Routing and layout, first pass
2024-01-01 Second pass
2024-01-08 Third pass
2024-01-13 Create LICENSE
2024-03-11 another quick pass
